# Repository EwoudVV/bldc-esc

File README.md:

# BLDC ESC

i'm building a small vesc like controller for BLDC and PMSM motors. the first motor is a 26V Groschopp gearmotor, but i want the board to be useful for other motors too. Hall control first, then FOC later

## status

the PCB is fully routed on four copper layers. it's 116 x 112 mm, with 449 component footprints on top and four mounting holes. the fitted BOM has 414 components across 110 different part numbers. KiCad reports zero DRC violations, zero open connections and no schematic mismatches. ERC is clean too

inner logic routing uses a 0.127 mm minimum. some control routes share the inner ground layer, and its filled ground pour stays connected. the USB pair has a continuous ground reference along its bottom-layer path, apart from the via transitions

the mounting holes, fabrication files and first bring-up firmware are done. PCBWay has the board and stencil files for review. the board hasn't been built, powered or tested. the final stack, USB impedance, cooling and some part availability still need checking before ordering

**don't manufacture the devlog 03 snapshot (`dcad1e4`).** the XT60 connections were backwards in that version. the current design has pad 1 as GND and pad 2 as VBUS

devlogs are on [Half Life](https://halflife.hackclub.com/projects/cmuveje4m009201rvgvsn2jbz) and synced to [JOURNAL.md](https://github.com/EwoudVV/bldc-esc/blob/main/JOURNAL.md)

## hardware

- STM32G474VET6 and DRV8353S gate driver
- six 60V bridge MOSFETs and three 1 milliohm current shunts
- INA241 current sensing, voltage sensing and temperature inputs
- hardware current protection, watchdog and brake chopper
- Hall and encoder inputs, analog throttle, RC PWM and digital controls
- CAN FD, UART, USB-C and SWD
- XT60 power input, MT60 motor pigtail and JST-GH signal connectors

## targets

- 12-30V input, mainly for 6S batteries and 24V systems
- 15A RMS phase current with passive cooling, 20A with extra cooling
- around 40A peak, with the allowed duration still to be worked out
- four layers, with 2 oz outer copper and 1 oz inner copper planned; exact stack pending PCBWay review

these current ratings are targets until thermal testing is done

## test motor

Groschopp / Blue-White BL6560-PS2120, P/N 930-23-9002:

- 26V, 0.75A nameplate
- 10W reducer output, 125 RPM, 6.68 in-lb torque
- 20:1 gearbox
- three phase leads and a separate sensor wire bundle

the OEM sensor pinout and motor measurements still need checking

## files

- `bldc-esc.kicad_pro`: open this in KiCad
- `schematic/`: the circuit sheets
- `bldc-esc.kicad_sym` and `bldc-esc.pretty/`: local symbols and footprints
- [bom.csv](bom.csv): component list, including the DNP flags

## mounting and assembly

there are four 3.2 mm non-plated holes for M3 mounting, on a 109 x 105 mm rectangle. each hole has a 7 mm copper keepout on every copper layer. use screw heads no larger than 6.4 mm and check the standoff clearance before fitting the board

the plan is to assemble one board myself at the makerspace with a stencil and reflow equipment. the top-only stencil is 0.10 mm thick and frameless. its paste file leaves out the seven DNP parts and keeps the segmented thermal-pad apertures. this is my first board with this kind of assembly, so i'll get help checking the paste and joints before powering it

## firmware

[firmware/BUILD.md](firmware/BUILD.md) has the build instructions, programming connections and UART commands. the first build can report input states and ADC readings, and read the gate driver's registers. ARM, all six PWM outputs and brake PWM stay low. the gate driver can only wake for register reads when the bus checks pass

the firmware builds for the STM32G474VET6. all three host tests passed, covering commands and measurements, reset outputs and UART input handling. it hasn't been flashed to a board. USB, CAN, motor commutation and FOC are still to come

## parts and fabrication

[the full purchasing BOM](manufacturing/BOM.md) has every part number, fitted and order quantities, vendor links, quotes and availability notes. the [purchasing CSV](manufacturing/purchasing-draft.csv) is the same detailed parts list in spreadsheet form. [BOM.md](BOM.md) is the grouped list synced from Half Life

quotes checked on October 11: five bare PCBWay boards are $311.90, the stencil is $10, and the component merchandise estimate is $191.29 before shipping, tax and discounts. the component figure includes backorders and unconfirmed offers. 100 of the 110 part numbers had confirmed stock; ten still need a source or delivery confirmation

the website list is $543.92 with its current shipping and tariff allowance. that is still an estimate, not a final checkout total. the full BOM explains the discounts, missing shipping quotes and difference from the supplier carts. nothing has been paid for. submission is paused while the over-budget form issue is sorted out

before ordering, PCBWay needs to confirm the 2 oz outer / 1 oz inner copper stack, layer-specific routing limits, small vias and 90 ohm USB pair. the quote form forces 8 mil globally even though the inner routing is 0.127 mm. the uploaded notes give the actual geometry, and a price and impedance review is pending

## manufacturing files

- [PCBWay package](manufacturing/pcbway-fabrication.zip): Gerbers, drills, top paste and order notes
- [Gerbers](manufacturing/bldc-esc-gerbers.zip): copper, mask, silkscreen, outline and drills
- [stencil package](manufacturing/stencil/bldc-esc-stencil.zip): top paste with the DNP apertures removed
- [schematic PDF](manufacturing/schematic.pdf): exported drawings for review
- [fitted parts](manufacturing/parts-one-board.csv): quantities for one assembled board
- [order settings](manufacturing/order-settings.json): stack, routing, mounting and quote details
- [design checks](manufacturing/design-checks.json): saved board checks

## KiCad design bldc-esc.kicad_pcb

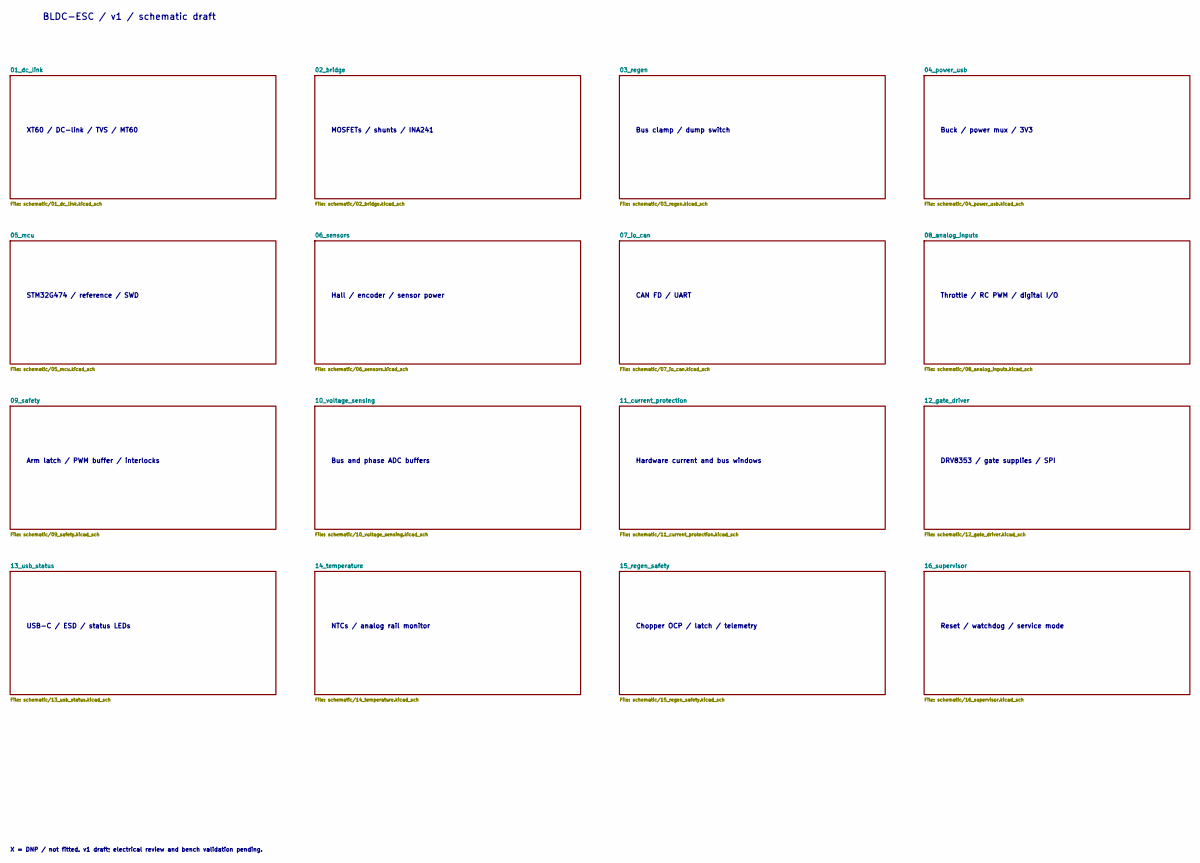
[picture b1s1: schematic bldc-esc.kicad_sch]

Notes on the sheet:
BLDC-ESC / v1 / schematic draft
XT60 / DC-link / TVS / MT60
MOSFETs / shunts / INA241
Bus clamp / dump switch
Buck / power mux / 3V3
STM32G474 / reference / SWD
Hall / encoder / sensor power
CAN FD / UART
Throttle / RC PWM / digital I/O
Arm latch / PWM buffer / interlocks
Bus and phase ADC buffers
Hardware current and bus windows
DRV8353 / gate supplies / SPI
USB-C / ESD / status LEDs
NTCs / analog rail monitor
Chopper OCP / latch / telemetry
Reset / watchdog / service mode
X = DNP / not fitted. v1 draft; electrical review and bench validation pending.

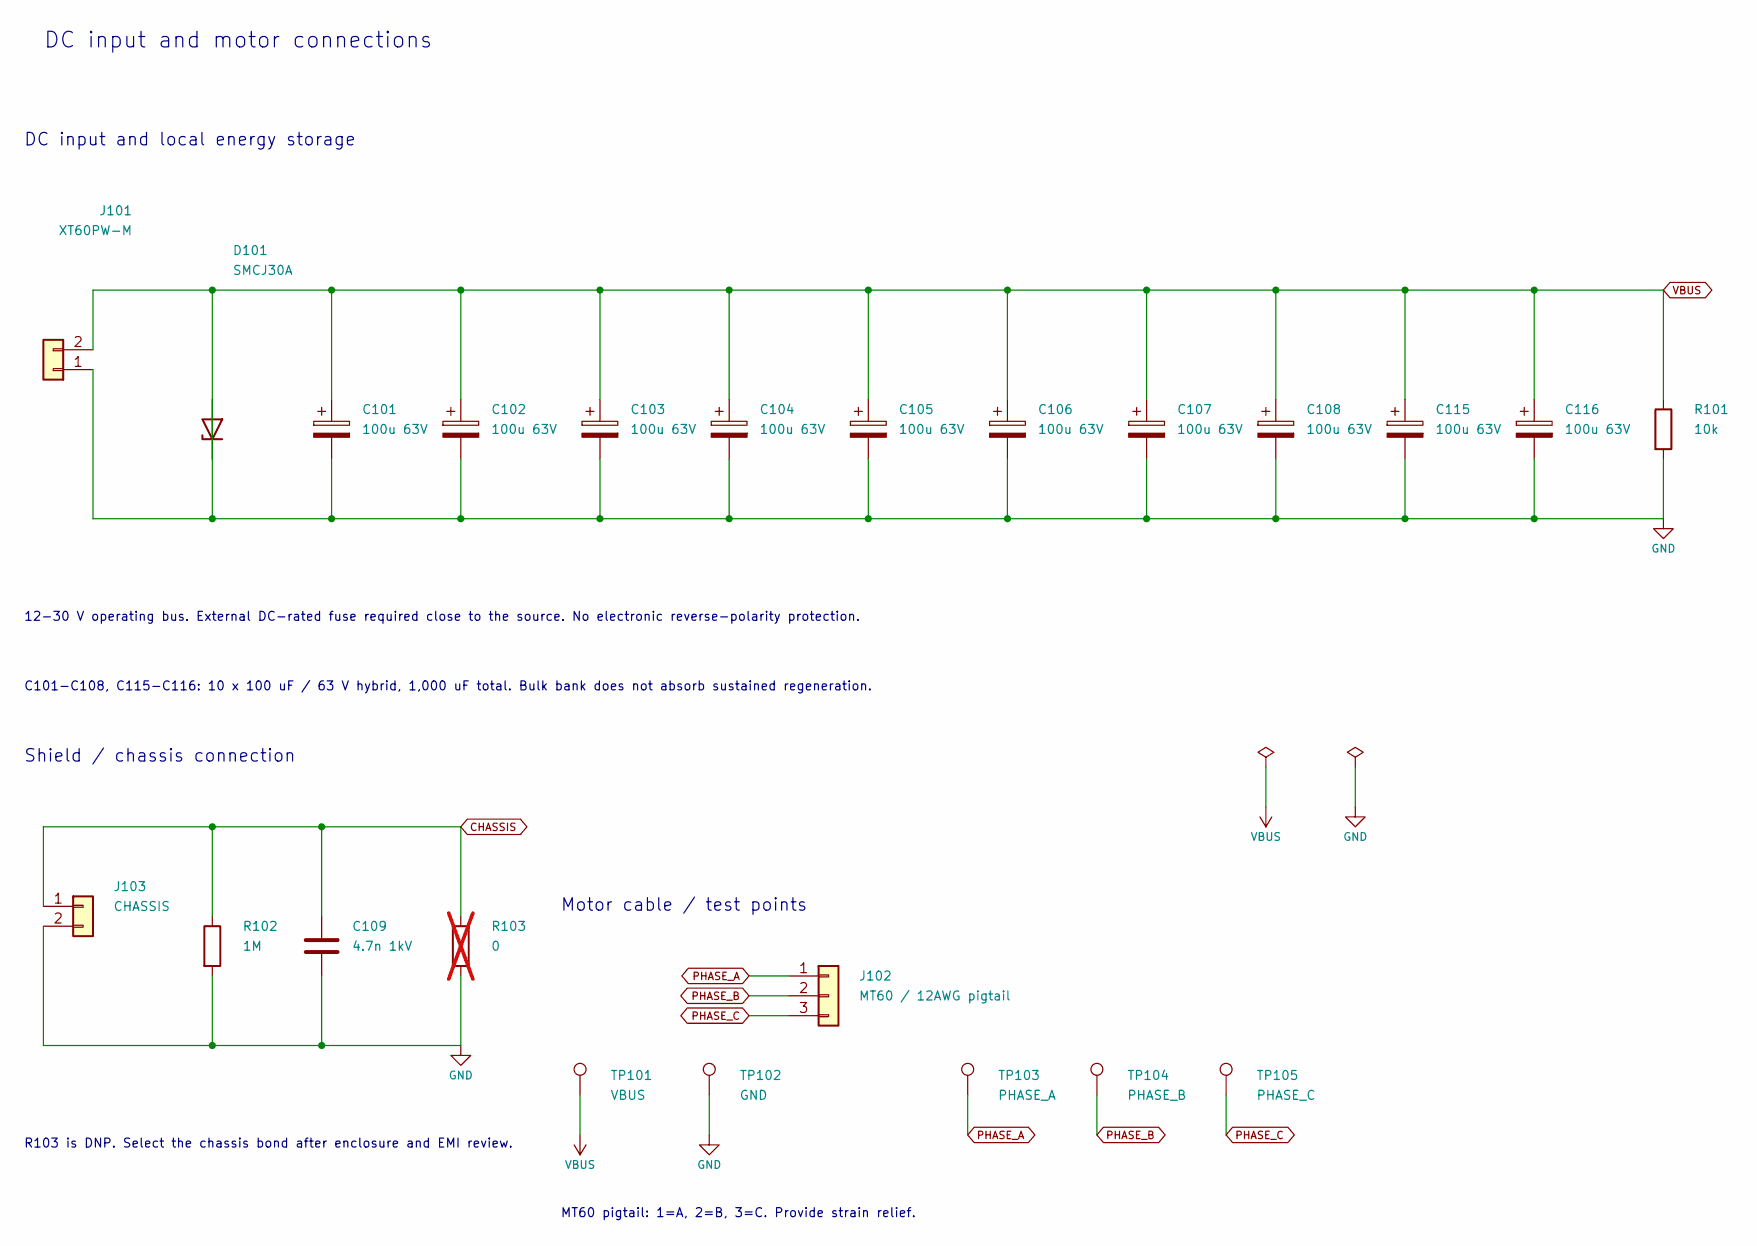
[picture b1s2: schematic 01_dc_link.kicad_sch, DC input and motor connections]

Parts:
C101, C102, C103, C104, C105, C106, C107, C108, C115, C116: 100u 63V; CP_Elec_10x12.5; MPN GXC1J101MCW1GS
C109: 4.7n 1kV; C_1206_3216Metric; MPN C1206C472KDRACTU
D101: SMCJ30A; D_SMC; MPN SMCJ30A
J101: XT60PW-M; XT60PW_M_Edge; MPN XT60PW-M
J102: MT60 / 12AWG pigtail; MT60_Pigtail_12AWG; MPN MT60-M
J103: CHASSIS; PinHeader_1x02_P2.54mm_Vertical; MPN M20-9990245
R101: 10k; R_1206_3216Metric; MPN RC1206FR-0710KL
R102: 1M; R_0603_1608Metric; MPN RC0603FR-071ML
R103: 0; R_0603_1608Metric; MPN RC0603JR-070RL; not fitted
TP101: VBUS; TestPoint_Pad_D1.5mm; MPN TESTPOINT
TP102: GND; TestPoint_Pad_D1.5mm; MPN TESTPOINT
TP103: PHASE_A; TestPoint_Pad_D1.5mm_NoSilk; MPN TESTPOINT
TP104: PHASE_B; TestPoint_Pad_D1.5mm_NoSilk; MPN TESTPOINT
TP105: PHASE_C; TestPoint_Pad_D1.5mm_NoSilk; MPN TESTPOINT

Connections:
CHASSIS: C109.1, J103.1, R102.1, R103.1; also elsewhere on the board
PHASE_A: J102.1, TP103.1 (1_1); also elsewhere on the board
PHASE_B: J102.2, TP104.1 (1_1); also elsewhere on the board
PHASE_C: J102.3, TP105.1 (1_1); also elsewhere on the board
VBUS: C101.1, C102.1, C103.1, C104.1, C105.1, C106.1, C107.1, C108.1, C115.1, C116.1, D101.1 (K), J101.2, R101.1, TP101.1 (1_1); also elsewhere on the board

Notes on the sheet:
DC input and motor connections
DC input and local energy storage
12-30 V operating bus. External DC-rated fuse required close to the source. No electronic reverse-polarity protection.
C101-C108, C115-C116: 10 x 100 uF / 63 V hybrid, 1,000 uF total. Bulk bank does not absorb sustained regeneration.
Shield / chassis connection
R103 is DNP. Select the chassis bond after enclosure and EMI review.
Motor cable / test points
MT60 pigtail: 1=A, 2=B, 3=C. Provide strain relief.

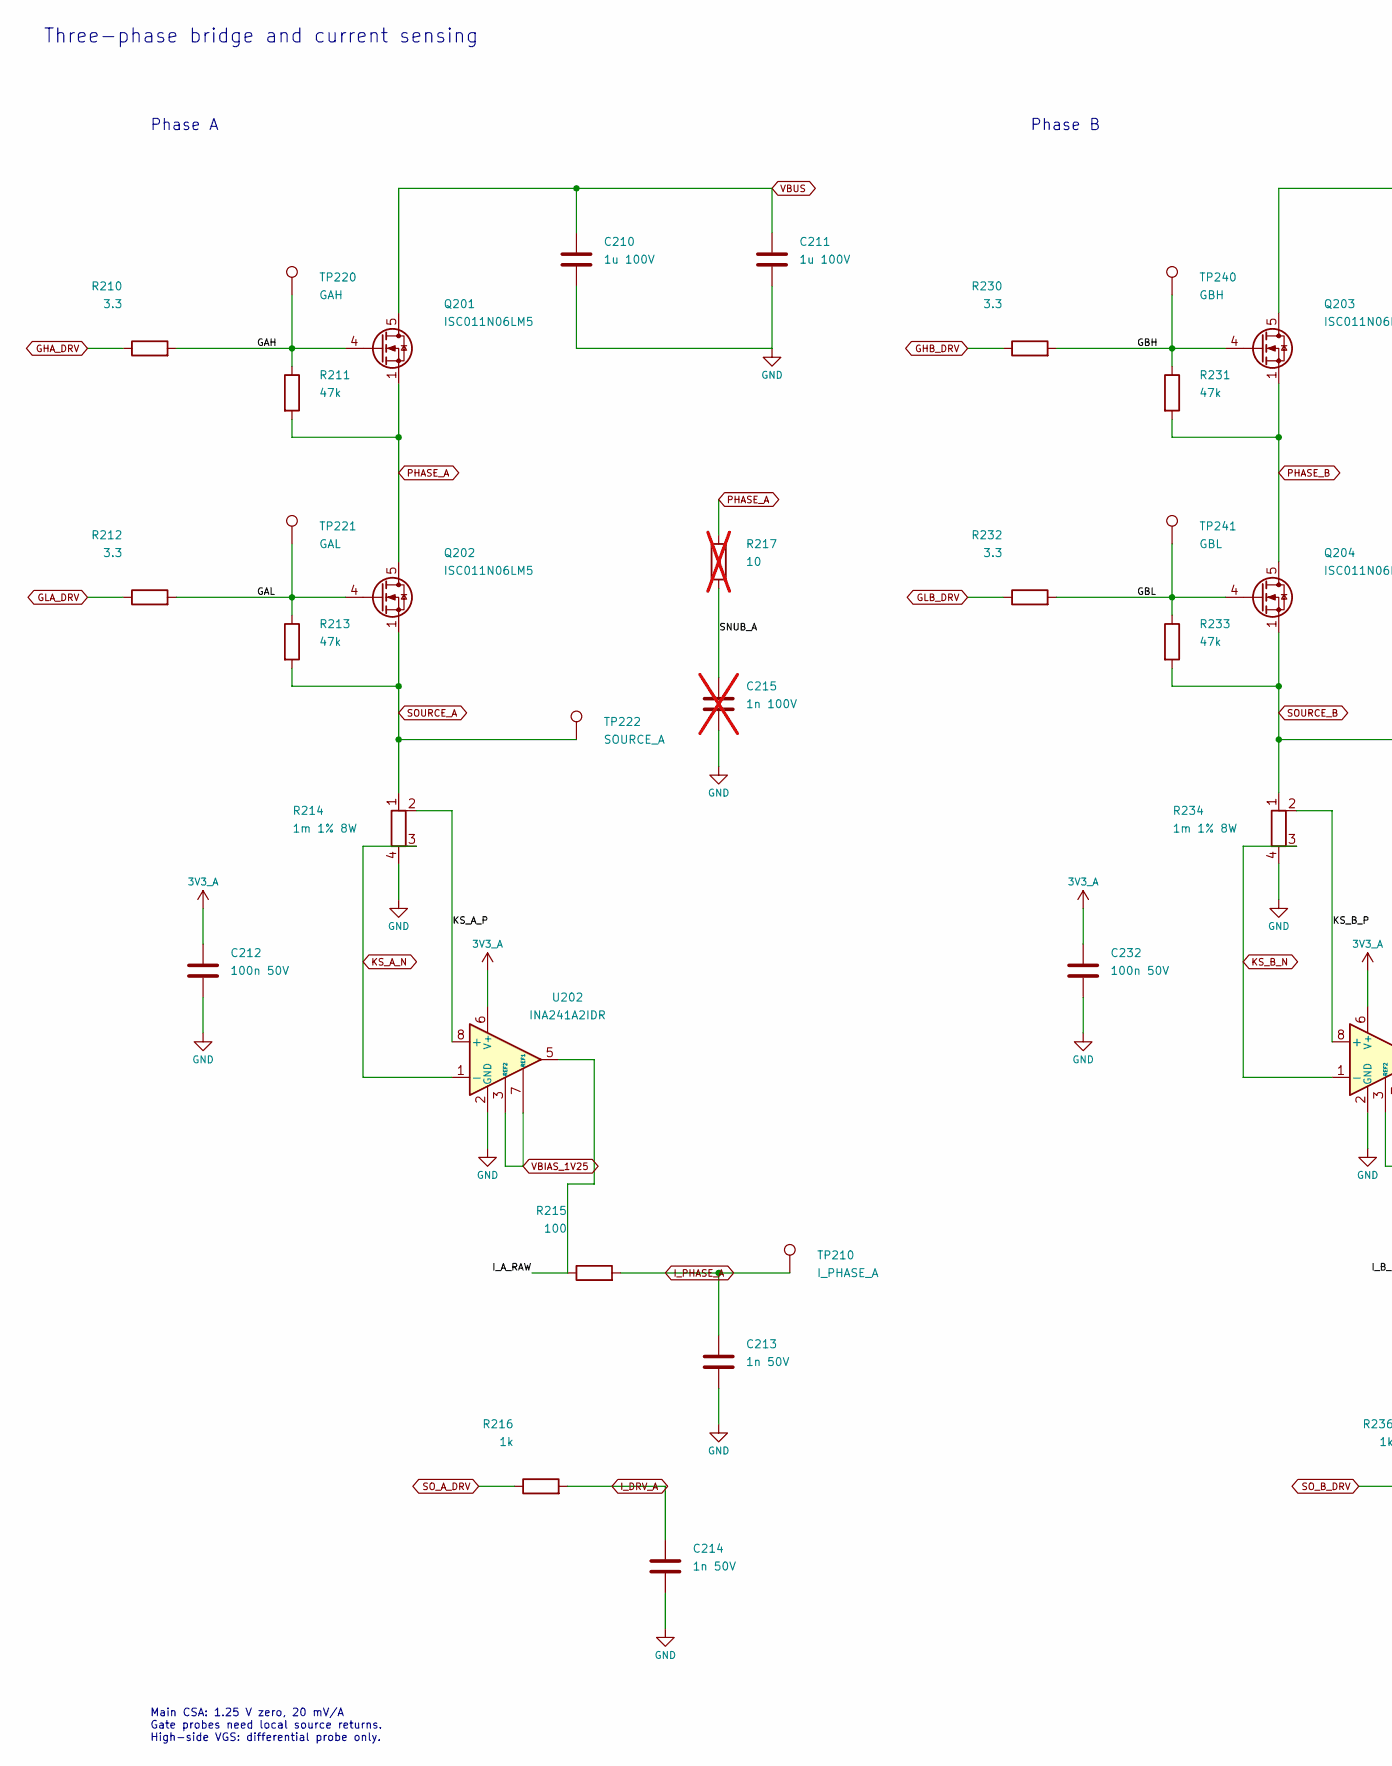
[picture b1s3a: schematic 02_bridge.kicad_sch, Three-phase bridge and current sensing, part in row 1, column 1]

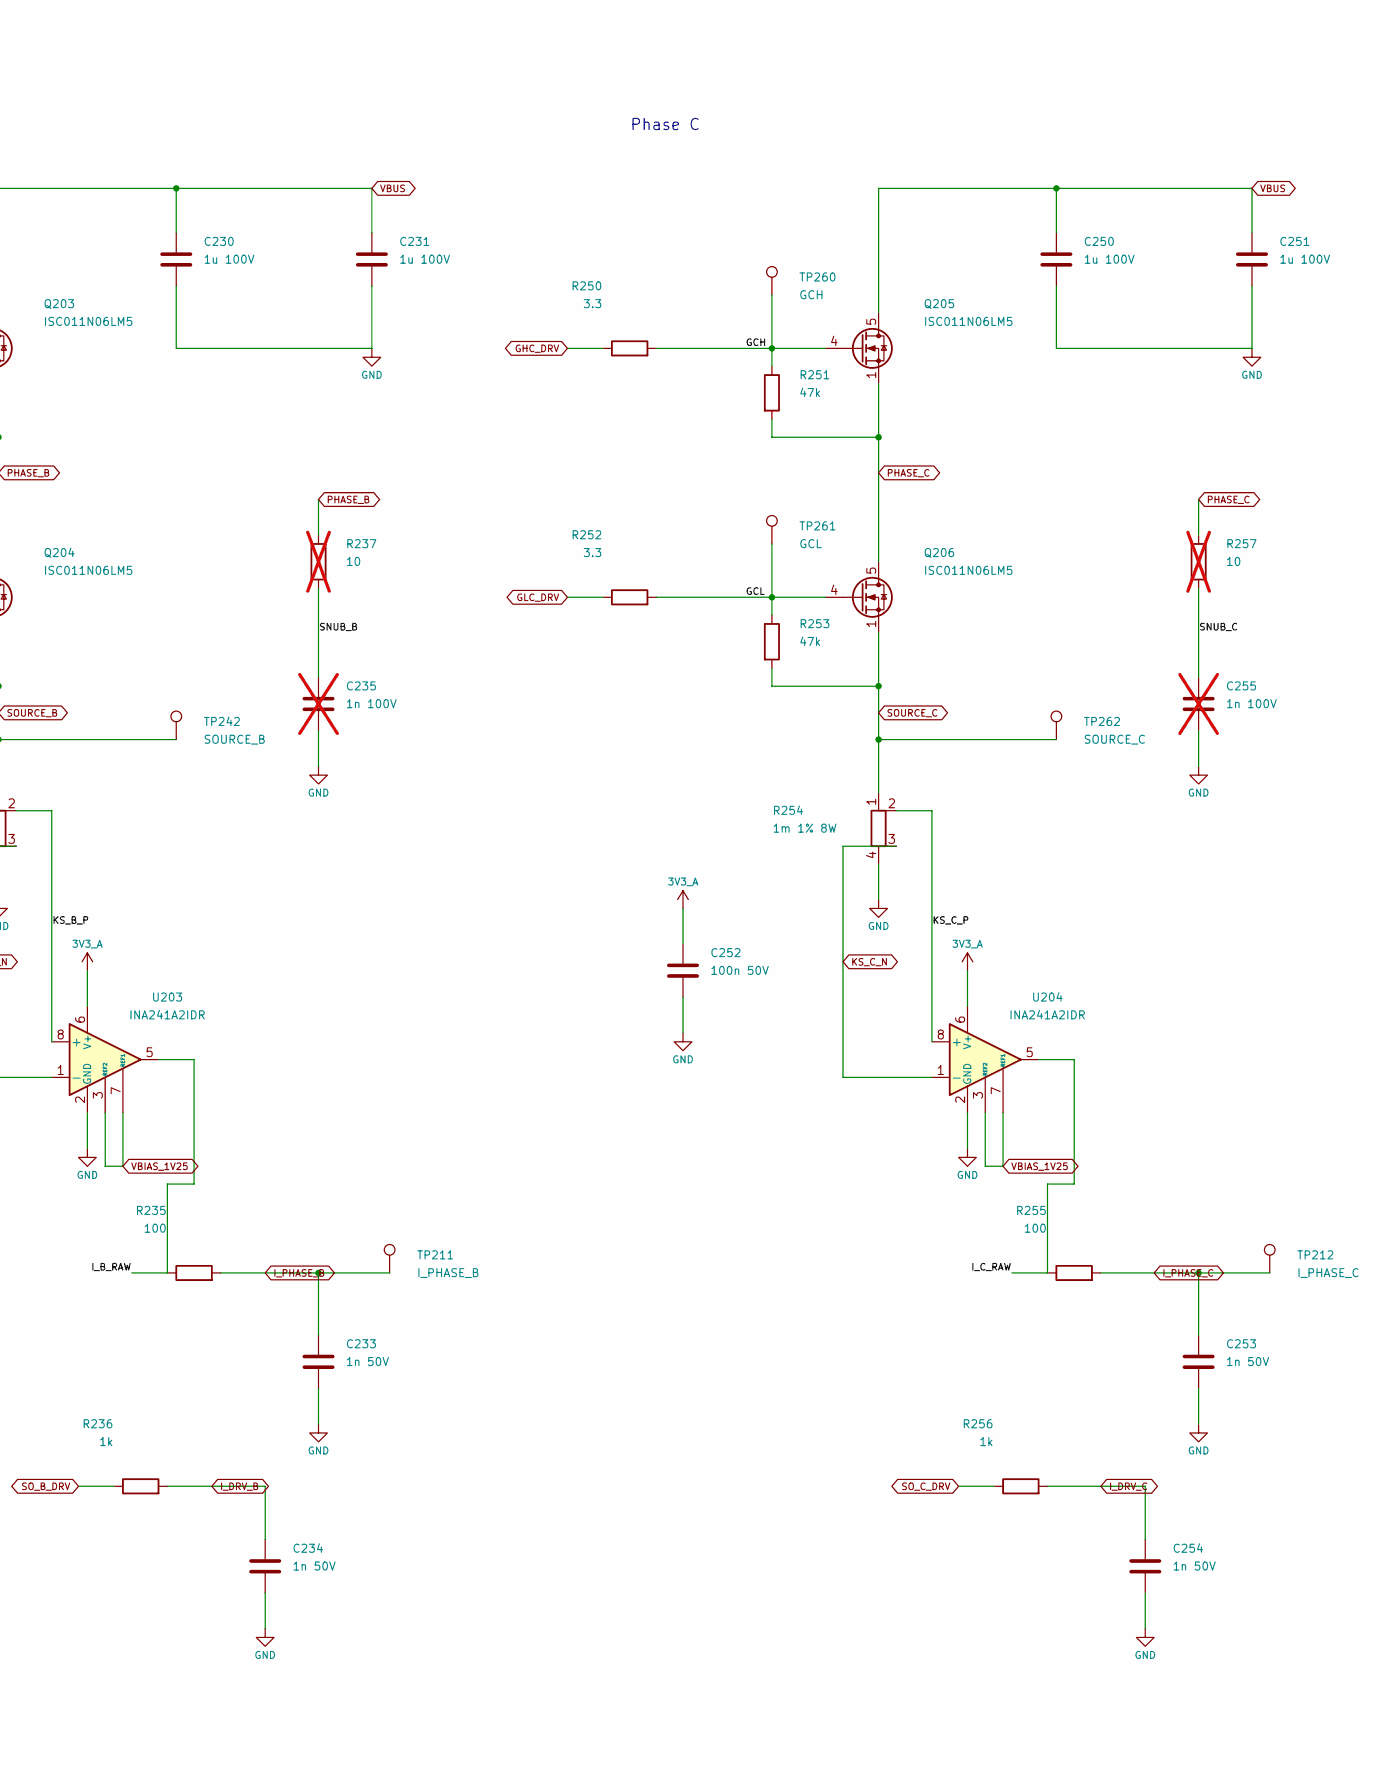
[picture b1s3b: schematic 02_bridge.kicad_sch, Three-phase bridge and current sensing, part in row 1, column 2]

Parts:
C210, C211, C230, C231, C250, C251: 1u 100V; C_1206_3216Metric; MPN C3216X7R2A105K160AA
C212, C232, C252: 100n 50V; C_0603_1608Metric; MPN C0603C104K5RACTU
C213, C214, C233, C234, C253, C254: 1n 50V; C_0603_1608Metric; MPN C0603C102J5GACTU
C215, C235, C255: 1n 100V; C_0805_2012Metric; MPN C0805C102J1GACTU; not fitted
Q201, Q202, Q203, Q204, Q205, Q206: ISC011N06LM5; Infineon_PG-TDSON-8_6.15x5.15mm; MPN ISC011N06LM5ATMA1
R210, R212, R230, R232, R250, R252: 3.3; R_0603_1608Metric; MPN RC0603FR-073R3L
R211, R213, R231, R233, R251, R253: 47k; R_0603_1608Metric; MPN RC0603FR-0747KL
R214, R234, R254: 1m 1% 8W; CSS4J_4026; MPN CSS4J-4026R-1L00F
R215, R235, R255: 100; R_0603_1608Metric; MPN RC0603FR-07100RL
R216, R236, R256: 1k; R_0603_1608Metric; MPN RC0603FR-071KL
R217, R237, R257: 10; R_0805_2012Metric; MPN RC0805FR-0710RL; not fitted
TP210: I_PHASE_A; TestPoint_Pad_D1.5mm; MPN TESTPOINT
TP211: I_PHASE_B; TestPoint_Pad_D1.5mm; MPN TESTPOINT
TP212: I_PHASE_C; TestPoint_Pad_D1.5mm; MPN TESTPOINT
TP220: GAH; TestPoint_Pad_D1.5mm_NoSilk; MPN TESTPOINT
TP221: GAL; TestPoint_Pad_D1.5mm_NoSilk; MPN TESTPOINT
TP222: SOURCE_A; TestPoint_Pad_D1.5mm_NoSilk; MPN TESTPOINT
TP240: GBH; TestPoint_Pad_D1.5mm_NoSilk; MPN TESTPOINT
TP241: GBL; TestPoint_Pad_D1.5mm_NoSilk; MPN TESTPOINT
TP242: SOURCE_B; TestPoint_Pad_D1.5mm_NoSilk; MPN TESTPOINT
TP260: GCH; TestPoint_Pad_D1.5mm_NoSilk; MPN TESTPOINT
TP261: GCL; TestPoint_Pad_D1.5mm_NoSilk; MPN TESTPOINT
TP262: SOURCE_C; TestPoint_Pad_D1.5mm_NoSilk; MPN TESTPOINT
U202, U203, U204: INA241A2IDR; SOIC-8_3.9x4.9mm_P1.27mm; MPN INA241A2IDR

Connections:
3V3_A: C212.1, C232.1, C252.1, U202.6 (V+), U203.6 (V+), U204.6 (V+); also elsewhere on the board
/02_bridge/GAH: Q201.4 (G), R210.2, R211.1, TP220.1 (1_1)
/02_bridge/GAL: Q202.4 (G), R212.2, R213.1, TP221.1 (1_1)
/02_bridge/GBH: Q203.4 (G), R230.2, R231.1, TP240.1 (1_1)
/02_bridge/GBL: Q204.4 (G), R232.2, R233.1, TP241.1 (1_1)
/02_bridge/GCH: Q205.4 (G), R250.2, R251.1, TP260.1 (1_1)
/02_bridge/GCL: Q206.4 (G), R252.2, R253.1, TP261.1 (1_1)
/02_bridge/I_A_RAW: R215.1, U202.5
/02_bridge/I_B_RAW: R235.1, U203.5
/02_bridge/I_C_RAW: R255.1, U204.5
/02_bridge/KS_A_P: R214.2, U202.8 (+)
/02_bridge/KS_B_P: R234.2, U203.8 (+)
/02_bridge/KS_C_P: R254.2, U204.8 (+)
/02_bridge/SNUB_A: C215.1, R217.2
/02_bridge/SNUB_B: C235.1, R237.2
/02_bridge/SNUB_C: C255.1, R257.2
GHA_DRV: R210.1; also elsewhere on the board
GHB_DRV: R230.1; also elsewhere on the board
GHC_DRV: R250.1; also elsewhere on the board
GLA_DRV: R212.1; also elsewhere on the board
GLB_DRV: R232.1; also elsewhere on the board
GLC_DRV: R252.1; also elsewhere on the board
I_DRV_A: C214.1, R216.2; also elsewhere on the board
I_DRV_B: C234.1, R236.2; also elsewhere on the board
I_DRV_C: C254.1, R256.2; also elsewhere on the board
I_PHASE_A: C213.1, R215.2, TP210.1 (1_1); also elsewhere on the board
I_PHASE_B: C233.1, R235.2, TP211.1 (1_1); also elsewhere on the board
I_PHASE_C: C253.1, R255.2, TP212.1 (1_1); also elsewhere on the board
KS_A_N: R214.3, U202.1 (-); also elsewhere on the board
KS_B_N: R234.3, U203.1 (-); also elsewhere on the board
KS_C_N: R254.3, U204.1 (-); also elsewhere on the board
PHASE_A: Q201.1 (S), Q201.2 (S), Q201.3 (S), Q202.5 (D), R211.2, R217.1; also elsewhere on the board
PHASE_B: Q203.1 (S), Q203.2 (S), Q203.3 (S), Q204.5 (D), R231.2, R237.1; also elsewhere on the board
PHASE_C: Q205.1 (S), Q205.2 (S), Q205.3 (S), Q206.5 (D), R251.2, R257.1; also elsewhere on the board
SOURCE_A: Q202.1 (S), Q202.2 (S), Q202.3 (S), R213.2, R214.1, TP222.1 (1_1); also elsewhere on the board
SOURCE_B: Q204.1 (S), Q204.2 (S), Q204.3 (S), R233.2, R234.1, TP242.1 (1_1); also elsewhere on the board
SOURCE_C: Q206.1 (S), Q206.2 (S), Q206.3 (S), R253.2, R254.1, TP262.1 (1_1); also elsewhere on the board
SO_A_DRV: R216.1; also elsewhere on the board
SO_B_DRV: R236.1; also elsewhere on the board
SO_C_DRV: R256.1; also elsewhere on the board
VBIAS_1V25: U202.3 (REF2), U202.7 (REF1), U203.3 (REF2), U203.7 (REF1), U204.3 (REF2), U204.7 (REF1); also elsewhere on the board
VBUS: C210.1, C211.1, C230.1, C231.1, C250.1, C251.1, Q201.5 (D), Q203.5 (D), Q205.5 (D); also elsewhere on the board

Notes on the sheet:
Three-phase bridge and current sensing
Phase A
Main CSA: 1.25 V zero, 20 mV/A Gate probes need local source returns. High-side VGS: differential probe only.
Phase B
Phase C

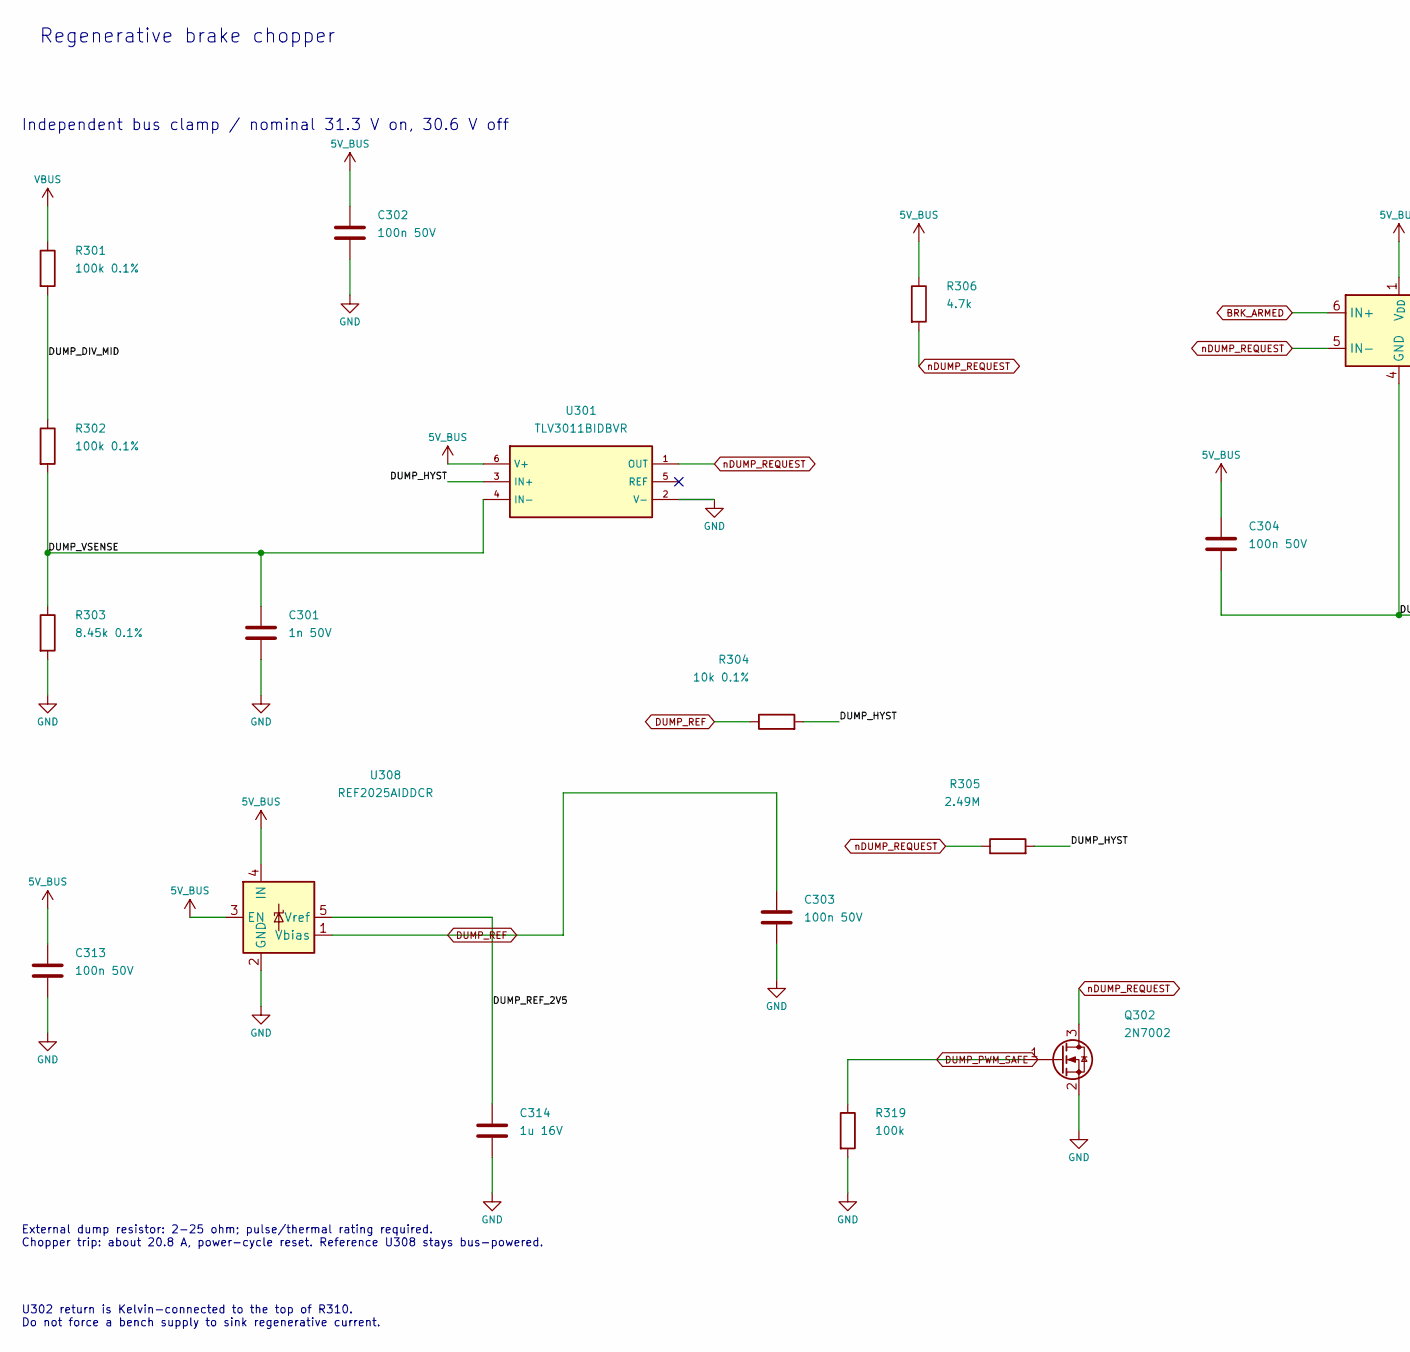
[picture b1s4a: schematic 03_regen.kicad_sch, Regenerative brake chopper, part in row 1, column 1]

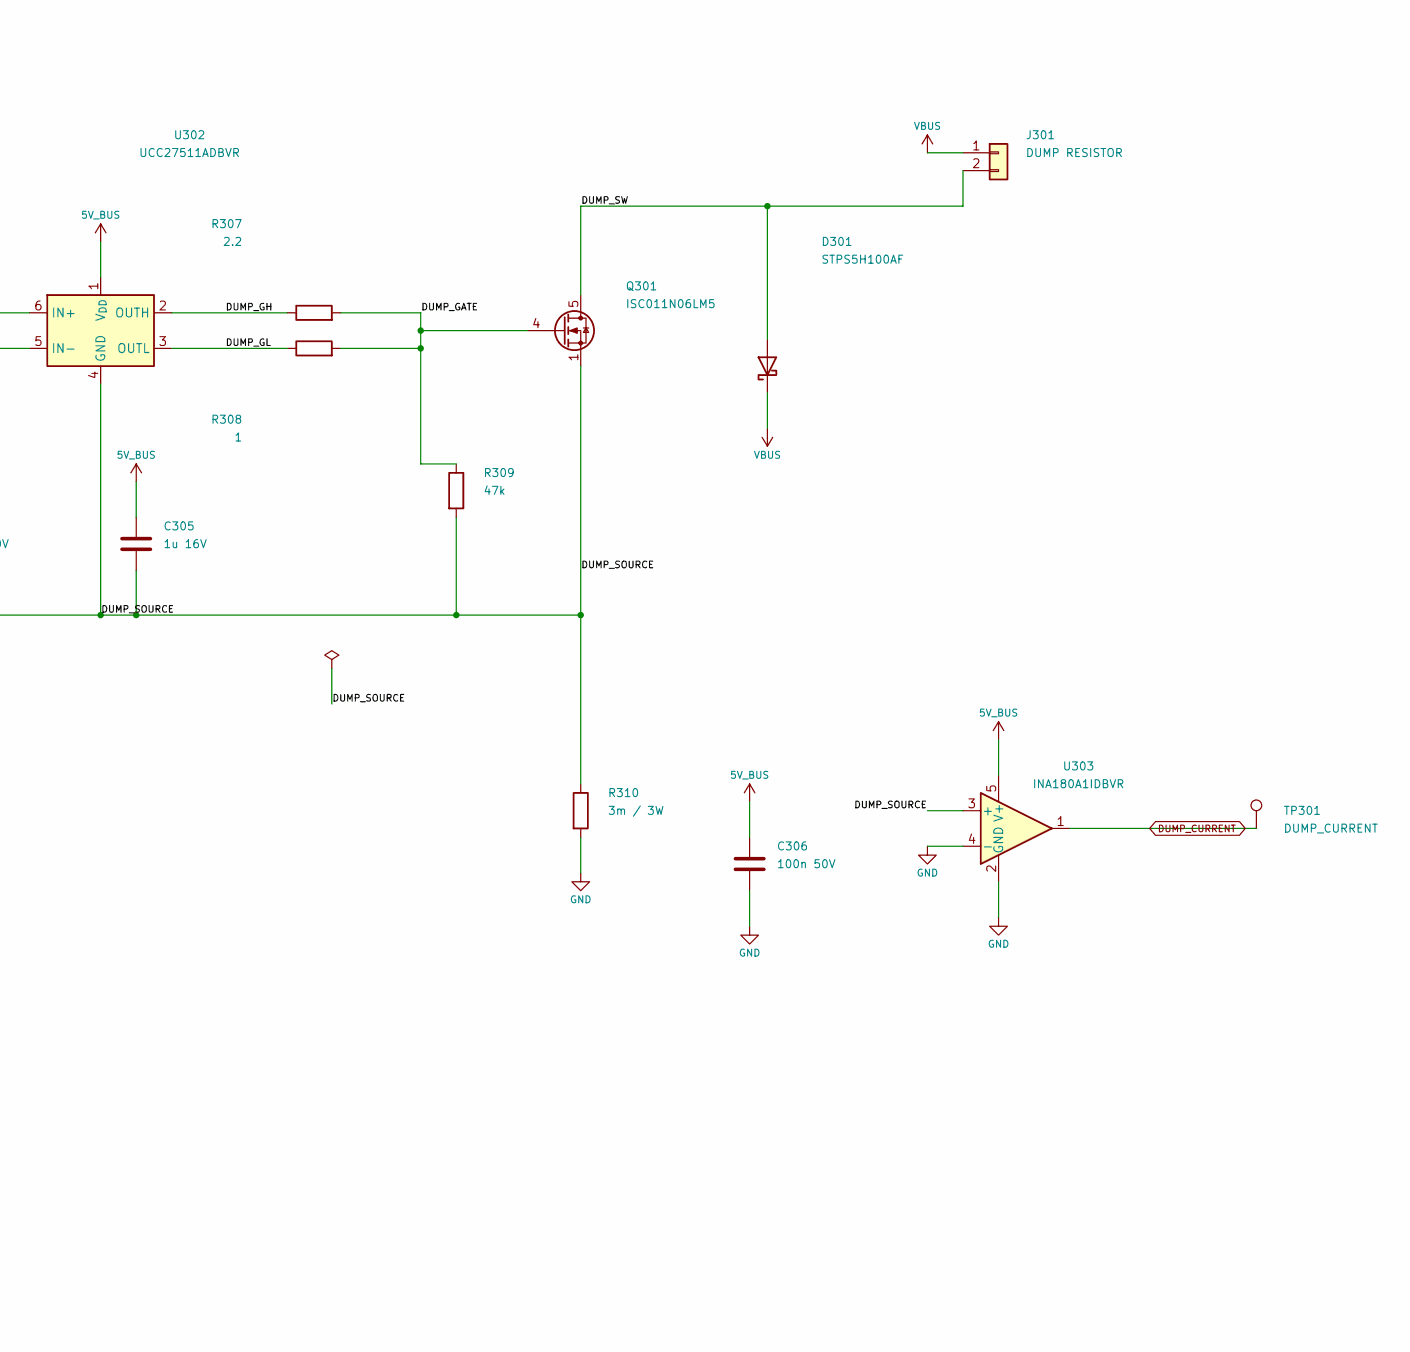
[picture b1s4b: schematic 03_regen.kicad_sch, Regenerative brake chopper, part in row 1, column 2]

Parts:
C301: 1n 50V; C_0603_1608Metric; MPN C0603C102J5GACTU
C302, C303, C304, C306, C313: 100n 50V; C_0603_1608Metric; MPN C0603C104K5RACTU
C305, C314: 1u 16V; C_0603_1608Metric; MPN C0603C105K4RACTU
D301: STPS5H100AF; D_SOD-128; MPN STPS5H100AF
J301: DUMP RESISTOR; TerminalBlock_Phoenix_MKDS-3-2-5.08_1x02_P5.08mm_Horizontal; MPN 1711725
Q301: ISC011N06LM5; Infineon_PG-TDSON-8_6.15x5.15mm; MPN ISC011N06LM5ATMA1
Q302: 2N7002; SOT-23; MPN 2N7002P,215
R301, R302: 100k 0.1%; R_0603_1608Metric; MPN RT0603BRD07100KL
R303: 8.45k 0.1%; R_0603_1608Metric; MPN RT0603BRD078K45L
R304: 10k 0.1%; R_0603_1608Metric; MPN RT0603BRD0710KL
R305: 2.49M; R_0603_1608Metric; MPN RC0603FR-072M49L
R306: 4.7k; R_0603_1608Metric; MPN RC0603FR-074K7L
R307: 2.2; R_0603_1608Metric; MPN RC0603FR-072R2L
R308: 1; R_0603_1608Metric; MPN RC0603FR-071RL
R309: 47k; R_0603_1608Metric; MPN RC0603FR-0747KL
R310: 3m / 3W; R_2512_6332Metric; MPN WSLP25123L000FEA
R319: 100k; R_0603_1608Metric; MPN RC0603FR-07100KL
TP301: DUMP_CURRENT; TestPoint_Pad_D1.5mm; MPN TESTPOINT
U301: TLV3011BIDBVR; SOT-23-6; MPN TLV3011BIDBVR
U302: UCC27511ADBVR; SOT-23-6; MPN UCC27511ADBVR
U303: INA180A1IDBVR; SOT-23-5; MPN INA180A1IDBVR
U308: REF2025AIDDCR; SOT-23-5; MPN REF2025AIDDCR

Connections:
5V_BUS: C302.1, C304.1, C305.1, C306.1, C313.1, R306.1, U301.6 (V+), U302.1 (V_{DD}), U303.5 (V+), U308.3 (EN), U308.4 (IN); also elsewhere on the board
/03_regen/DUMP_DIV_MID: R301.2, R302.1
/03_regen/DUMP_GATE: Q301.4 (G), R307.2, R308.2, R309.1
/03_regen/DUMP_GH: R307.1, U302.2 (OUTH)
/03_regen/DUMP_GL: R308.1, U302.3 (OUTL)
/03_regen/DUMP_HYST: R304.2, R305.2, U301.3 (IN+)
/03_regen/DUMP_REF_2V5: C314.1, U308.5 (Vref)
/03_regen/DUMP_SOURCE: C304.2, C305.2, Q301.1 (S), Q301.2 (S), Q301.3 (S), R309.2, R310.1, U302.4 (GND), U303.3 (+)
/03_regen/DUMP_SW: D301.2 (A), J301.2, Q301.5 (D)
/03_regen/DUMP_VSENSE: C301.1, R302.2, R303.1, U301.4 (IN-)
BRK_ARMED: U302.6 (IN+); also elsewhere on the board
DUMP_CURRENT: TP301.1 (1_1), U303.1; also elsewhere on the board
DUMP_PWM_SAFE: Q302.1 (G), R319.1; also elsewhere on the board
DUMP_REF: C303.1, R304.1, U308.1 (Vbias); also elsewhere on the board
VBUS: D301.1 (K), J301.1, R301.1; also elsewhere on the board
nDUMP_REQUEST: Q302.3 (D), R305.1, R306.2, U301.1 (OUT), U302.5 (IN-); also elsewhere on the board

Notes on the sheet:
Regenerative brake chopper
Independent bus clamp / nominal 31.3 V on, 30.6 V off
External dump resistor: 2-25 ohm; pulse/thermal rating required. Chopper trip: about 20.8 A, power-cycle reset. Reference U308 stays bus-powered.
U302 return is Kelvin-connected to the top of R310. Do not force a bench supply to sink regenerative current.
